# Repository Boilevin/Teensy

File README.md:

# Software for the TeensyMower
- You will need the Software for the Teensy from File Teensymower.
- If you don't want to used RFID, you can use ESP32_WIFI_Passerrelle for the ESP32.
- If you want to used RFID and MQTT, you can use ESP32_RFID_mqtt

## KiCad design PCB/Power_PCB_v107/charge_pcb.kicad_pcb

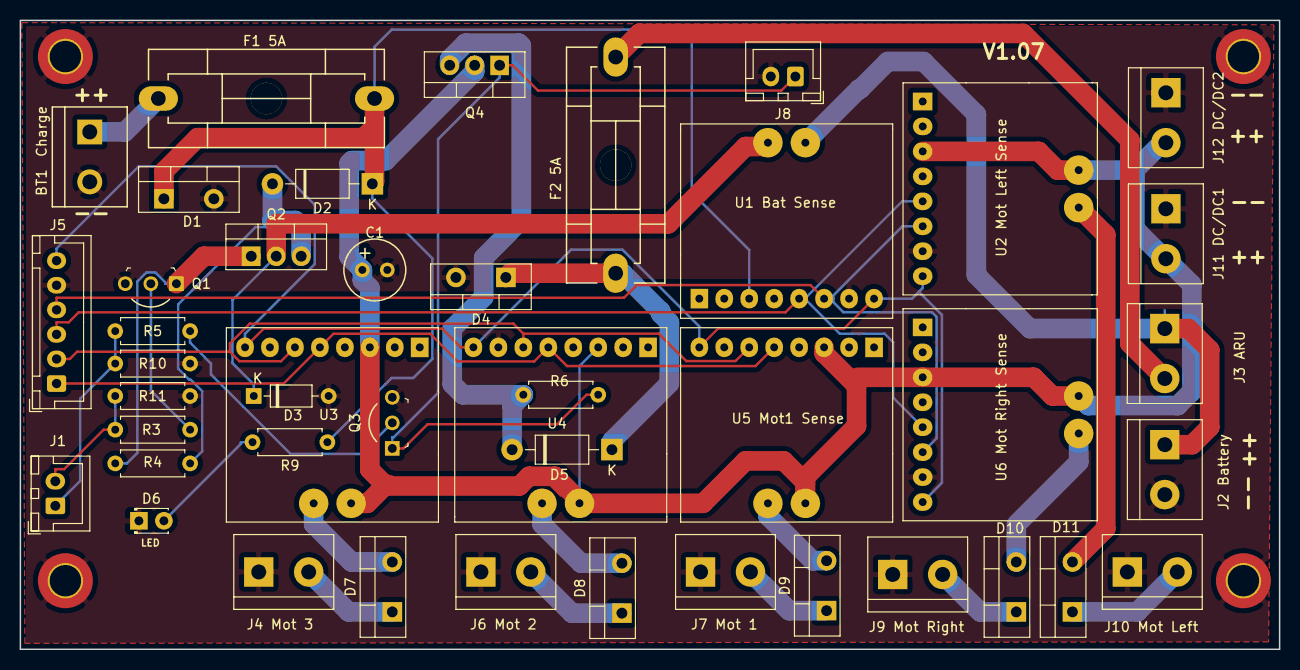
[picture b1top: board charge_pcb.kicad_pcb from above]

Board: 2 copper layers, 128.1 x 64.0 mm, 48 parts (0 on the bottom side), 32 nets.

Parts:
BT1: Charge; Anschlussklemme_2P_RM5,08
C1: 100uF; Elko_vert_11.2x6.3mm_RM2.5
D1, D4, D7, D8, D9, D10, D11: MBR1045; TO-220-2_Vertical
D2, D5: SB1240; D_DO-41_SOD81_P10.16mm_Horizontal
D3: NOT USE; D_DO-35_SOD27_P7.62mm_Horizontal
D6: LED; LED_D1.8mm_W3.3mm_H2.4mm
F1 5A: 5A; Fuseholder_Reichelt_PL112000
F2 5A: 10A; Fuseholder_Reichelt_PL112000
H1, H2, H3, H4: MountingHole_Pad; MountingHole_3.2mm_M3_DIN965_Pad_TopBottom
J1: Main_PCB2; JST_XH_B2B-XH-A_1x02_P2.50mm_Vertical
J2 Battery: Battery; TerminalBlock_bornier-2_P5.08mm
J3 ARU: Power Switch; TerminalBlock_bornier-2_P5.08mm
J4 Mot 3: Mow3; TerminalBlock_bornier-2_P5.08mm
J5: Main_PCB1; JST_XH_B6B-XH-A_1x06_P2.50mm_Vertical
J6 Mot 2: Mow2; TerminalBlock_bornier-2_P5.08mm
J7 Mot 1: Mow1; TerminalBlock_bornier-2_P5.08mm
J8: Start; JST_XH_B2B-XH-A_1x02_P2.50mm_Vertical
J9 Mot Right: Mot_Right; TerminalBlock_bornier-2_P5.08mm
J10 Mot Left: Mot_Left; TerminalBlock_bornier-2_P5.08mm
J11 DC/DC1: DC/DC1; TerminalBlock_bornier-2_P5.08mm
J12 DC/DC2: DC/DC2; TerminalBlock_bornier-2_P5.08mm
Q1, Q3: BC547C; TO-92-3_Formed_Leads
Q2, Q4: IRF9540N; TO-220-3_Vertical
R3, R4, R5, R6, R10, R11: 4k7; R_Axial_DIN0207_L6.3mm_D2.5mm_P7.62mm_Horizontal
R9: 4.7kO; R_Axial_DIN0207_L6.3mm_D2.5mm_P7.62mm_Horizontal
U1 Bat Sense, U2 Mot Left Sense, U3, U4, U5 Mot1 Sense, U6 Mot Right Sense: INA226

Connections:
+3V3: J5.6, U1 Bat Sense.8, U2 Mot Left Sense.8, U3.8, U4.8, U5 Mot1 Sense.8, U6 Mot Right Sense.8
GND: BT1.2, C1.2, D1.2, D3.2, D4.2, D6.1, H1.1, H2.1, H3.1, H4.1, J2 Battery.2, J4 Mot 3.1, J5.5, J6 Mot 2.1, J7 Mot 1.1, J8.2, J9 Mot Right.1, J10 Mot Left.1, J11 DC/DC1.1, J12 DC/DC2.1, Q1.3, Q3.3, R10.2, R11.2, U1 Bat Sense.7, U2 Mot Left Sense.7, U3.7, U4.7, U5 Mot1 Sense.7, U6 Mot Right Sense.7
unnamed: BT1.1, F1 5A.1
unnamed: D2.2, Q2.3, R4.1
unnamed: D3.1, Q2.2, U1 Bat Sense.9
unnamed: D4.1, D5.1, F2 5A.2
unnamed: D5.2, Q4.3, R6.1
unnamed: D6.2, R9.2
unnamed: D7.1, J4 Mot 3.2
unnamed: D7.2, U3.10
unnamed: D8.1, J6 Mot 2.2
unnamed: D8.2, U4.10
unnamed: D9.1, J7 Mot 1.2
unnamed: D9.2, U5 Mot1 Sense.10
unnamed: D10.1, J9 Mot Right.2
unnamed: D10.2, U6 Mot Right Sense.10
unnamed: D11.1, J10 Mot Left.2
unnamed: D11.2, U2 Mot Left Sense.10
unnamed: F2 5A.1, J3 ARU.2
unnamed: J2 Battery.1, J3 ARU.1, U1 Bat Sense.10
unnamed: J8.1, Q3.1, Q4.1, R6.2
unnamed: Q1.1, Q2.1, R4.2
unnamed: Q1.2, R3.1
unnamed: Q3.2, R5.2
SCL0: J5.3, U1 Bat Sense.5, U2 Mot Left Sense.5, U6 Mot Right Sense.5
SCL1: J5.1, U3.5, U4.5, U5 Mot1 Sense.5
SDA0: J5.4, U1 Bat Sense.6, U2 Mot Left Sense.6, U6 Mot Right Sense.6
SDA1: J5.2, U3.6, U4.6, U5 Mot1 Sense.6
V_Bat: C1.1, J11 DC/DC1.2, J12 DC/DC2.2, Q4.2, U2 Mot Left Sense.3, U2 Mot Left Sense.9, U3.3, U3.9, U4.3, U4.9, U5 Mot1 Sense.3, U5 Mot1 Sense.9, U6 Mot Right Sense.3, U6 Mot Right Sense.9
V_Charge: D1.1, D2.1, F1 5A.2, R9.1, U1 Bat Sense.3
pinBatterySwitch: J1.1, R5.1, R10.1
pinChargeEnable: J1.2, R3.2, R11.1

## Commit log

2021-08-05 init
2021-08-08 work1
2021-08-09 move file
2021-08-09 add pcb
2021-08-29 ina226and per
    Perimeter and Ina226 added
2021-09-06 update01
2021-09-18 charging ok
2021-09-20 update pdf
2021-09-26 esp32 part
2021-09-30 robomow version
2021-10-31 tracking direction
2021-11-08 ina226 calibration
2021-11-15 rfid
2021-11-22 wifi
2021-12-03 rfid update
2021-12-03 Formate the Files
    Only Code formating
2021-12-03 Update perimeter.cpp
    Remove the static from void
2021-12-03 Update INA226.cpp
    remove ; on #endif; twice
2021-12-03 Compilation error
    Compilation error
2021-12-04 Update config_example.h
    Change order in File
2021-12-04 Update config_example.h
    Add config from mower.cpp
2021-12-04 Change mower.cpp
    Change mower.cpp and change . to _ Compiler Errors
2021-12-04 Small Tipo
2021-12-05 rfid ok
2021-12-05 mqtt part
2021-12-05 mqtt using esp32
2021-12-08 mqtt explicit
2021-12-11 mqtt finish
2021-12-12 cleanning
    Auto swap to ESP32 AP
2021-12-14 BL motor
    Add the motor driver selection
    BL500W not tested
2021-12-15 oled screen
2021-12-16 pwm frequency
2021-12-16 Add Header
2021-12-16 Update drivers.cpp
    Change order
2021-12-16 Update drivers.cpp
    Remove unused Drivers
2021-12-16 temperature
2021-12-21 odometry
2021-12-29 console
2022-01-30 1mowmotoroption
2022-02-04 wiring
2022-02-12 watchdog imu
2022-02-19 piardu for teensy
2022-02-19 flash process
2022-02-20 piardu
2022-02-21 gps work
2022-02-25 Code optimization
2022-02-25 Add Bernards last changes
2022-02-25 Add Bernards changes
2022-02-25 Remove unused Code
2022-02-25 Test for WIFI Connection Clients
2022-02-26 Change Wifi Connection
    Tested and now it is stable
2022-03-04 swapmotor direction
2022-03-21 minor_change
2022-03-27 bat management
2022-04-01 perimeter_filter
2022-04-10 te
    flash teensy using PI
2022-04-19 screen etc
2022-04-23 docking
    manual mow start
    station check update
    imu tilt 70 deg error
2022-05-03 2coil
    start the coil dev
2022-05-07 web server
    Initial work on web server
2022-05-08 sdcard log
    add teensy sdcard logger
2022-05-09 starting point
2022-05-09 Update TeensyMowerWebControl_ESP32.ino
    change version date
2022-05-12 new pfod
2022-05-23 SDCARD
    Create the pfod menu to read the teensy sd card log
2022-05-24 sdcard
    sdcard log management from pfod
2022-05-27 sdcard02
    end of sdcard card prog log
2022-05-30 pfod
    pfod speed set to 19200 to avoid buffer error over wifi.New heading offset into command menu
2022-06-11 test
2022-07-09 3d file
2022-08-28 yardforce addon
    Solved:
    motor calibration issue.
    reduce speed near perimeter.
    cover management
2022-09-01 platform management
    add platform selection into mower.h to avoid changing mower.cpp and mower.h
2022-09-23 swap coil polarity bug
2022-10-05 brake selection
2022-11-12 v421
    New manual mangement.
    Power off pcb at end charging if no timer active
    No reverse in random mowing.
    Rev distance setting into bumper
    Multiple mower platform on factory setting
    bug in factory setting : Reverse the left and right in bylane
2022-11-12 remove test text
2023-04-29 speed
    error in bt baudrate
2023-05-05 zs-x12
    add zs-x12 driver support for wheel drive
2023-05-06 odometry limit for zs-x12
2023-05-15 Update mower.cpp
    add pwm offset to have the same speed on 2 wheel
2023-06-14 battery
    add a max charging duration into pfod
2023-06-25 battery version
    On PCB without charging battery jumper .PCB power off at the end of charging if no timer.
    If timer adjust the max charging duration > at the delay between 2 mowing planning
2023-06-27 timer battery
2023-07-27 warning
2023-08-03 timer_start
    timer can start mower if the battery is not fully charge ,new setting into battery menu
2024-03-13 esp32 bt passerelle
2024-05-19 V490
    Change management of roll to track
    add the sonar in tracking mode (not tested)
2024-05-20 v491
    add detection on lost signal
2024-05-22 v492
    SDCard deactivate is not working correctly
2024-05-23 cosmetics
    Sd card enable into pfod info menu
2024-06-04 v493
    sefanH bug in rear bumper
2024-06-12 Update robot.cpp
    Issue: After reverse and roll coil is just upper the wire ,so signal magnitude is very small
    Sol:change the location of sender running test after the forward movement
2024-06-26 mi6323d
2024-07-20 v494
2024-07-20 v495
    smooth accel after sonar trig
    add test sonar trig into pfod
    add slider setting for sonar speed coeff into pfod
    add voltage adjust for charge and battery into firmware
    Not tested with sonar
2024-07-28 v496
    move actual heading to bylane setting page to avoid PFOD issue.
    Change motor RPM PID control for better slope management on no friction BL motor.
    Reduce roll speed in end of lane for better accuracy.
2024-08-07 speed adjust on roll
2025-05-03 v497 powerpcb small
    Add code to select powerpcb small to control only 1 mow motor and use only 1 I2C line.
    Connection is made on I2C1 on mainPCB connector I2C0 is not use.
2025-05-11 V497
    esp32 update to last compiler version.
    esp32 sender wifi add response for mower side
